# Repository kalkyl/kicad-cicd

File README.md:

# KiCad v6 CI/CD workflow example

Minimal example of a `KiBot` workflow for `KiCad v6` to automatically generate:

- PDF schematics
- Interactive HTML BOM

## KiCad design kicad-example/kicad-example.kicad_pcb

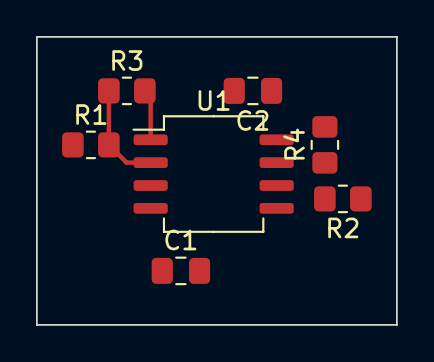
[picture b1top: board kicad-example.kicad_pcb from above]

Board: 2 copper layers, 20.0 x 16.0 mm, 7 parts (0 on the bottom side), 7 nets.

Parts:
C1, C2: 10u; C_0805_2012Metric_Pad1.18x1.45mm_HandSolder
R1, R2, R3, R4: 10k; R_0805_2012Metric_Pad1.20x1.40mm_HandSolder
U1: TL072; SO-8_5.3x6.2mm_P1.27mm

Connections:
GND: C1.2, C2.2, U1.3 (+), U1.5 (+)
unnamed: R1.2, R3.1, U1.2 (-)
unnamed: R2.2, R4.1, U1.6 (-)
OUT_A: R3.2, U1.1
OUT_B: R4.2, U1.7
VDD: C1.1, U1.4 (V-)
VSS: C2.1, U1.8 (V+)

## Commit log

2022-04-08 Init
2022-04-08 Workflow
2022-04-08 Route
2022-04-08 Schematic file path
2022-04-09 Readme
